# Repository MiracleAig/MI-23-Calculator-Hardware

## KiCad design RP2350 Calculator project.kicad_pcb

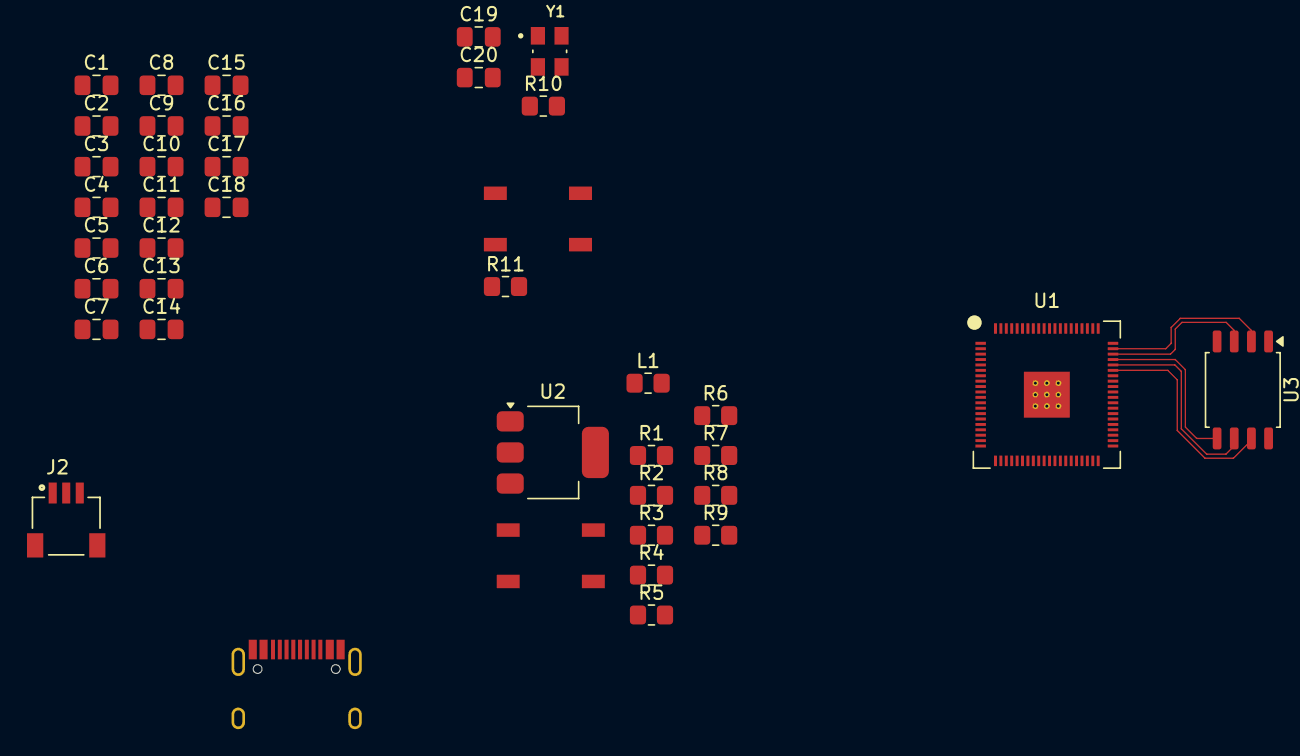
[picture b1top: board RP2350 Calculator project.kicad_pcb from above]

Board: 2 copper layers, 40 parts (0 on the bottom side), 28 nets.

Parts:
C1, C2, C3, C16: 4.7uF; C_0805_2012Metric_Pad1.18x1.45mm_HandSolder
C4, C5: 10u; C_0805_2012Metric_Pad1.18x1.45mm_HandSolder
C6, C7, C8, C9, C10, C11, C12, C13, C14, C15, C17, C18: 100n; C_0805_2012Metric_Pad1.18x1.45mm_HandSolder
C19, C20: 15pF; C_0805_2012Metric_Pad1.18x1.45mm_HandSolder
J1: USB_C_Receptacle_USB2.0_14P; USB_C_HRO_TYPE-C-31-M-12
J2: SM03B-SRSS-TB_LF__SN_; JST_SM03B-SRSS-TB_LF__SN_
L1: 3.3u; R_0805_2012Metric_Pad1.20x1.40mm_HandSolder
R1: 33; R_0805_2012Metric_Pad1.20x1.40mm_HandSolder
R2, R3: 5.1K; R_0805_2012Metric_Pad1.20x1.40mm_HandSolder
R4, R5: 27; R_0805_2012Metric_Pad1.20x1.40mm_HandSolder
R6, R7, R8: DNF; R_0805_2012Metric_Pad1.20x1.40mm_HandSolder
R9, R10, R11: 1K; R_0805_2012Metric_Pad1.20x1.40mm_HandSolder
SW1, SW2: SW_Push; Button_TL3342
U1: RP2350A-QFN60; RP2350B_QFN-80_EP_10.573x10.573_Pitch0.4mm
U2: NCP1117-3.3_SOT223; NCP1117_3V3
U3: W25Q128JVS
Y1: ABM8-272-T3; XTAL_ABM8-272-T3

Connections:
+1V1: C1.1, C15.1, C16.1, C17.1, L1.1, U1.6 (DVDD), U1.23 (DVDD), U1.39 (DVDD), U1.50 (VREG_FB)
+3V3: C2.1, C5.1, C6.1, C7.1, C8.1, C9.1, C10.1, C11.1, C12.1, C13.1, C14.1, C18.2, R1.1, R6.1, U1.1 (IOVDD), U1.11 (IOVDD), U1.20 (IOVDD), U1.30 (IOVDD), U1.38 (IOVDD), U1.44 (ADC_AVDD), U1.45 (IOVDD), U1.49 (VREG_VIN), U1.53 (USB_OTP_VDD), U1.54 (QSPI_IOVDD), U2.2 (VO), U3.8 (VCC)
D+: J1.A6 (D+), J1.B6 (D+), R4.1
D-: J1.A7 (D-), J1.B7 (D-), R5.2
GND: C1.2, C2.2, C3.2, C4.2, C5.2, C6.2, C7.2, C8.2, C9.2, C10.2, C11.2, C12.2, C13.2, C14.2, C15.2, C16.2, C17.2, C18.1, C19.1, C20.1, J1.A1 (GND), J1.A12 (GND), J1.B1 (GND), J1.B12 (GND), J1.S1 (SHIELD), J2.2, J2.S1 (SHIELD), J2.S2 (SHIELD), R2.2, R3.2, R11.1, SW1.1, U1.47 (VREG_PGND), U1.61 (GND), U2.1 (GND), U3.4 (GND), Y1.2 (GND), Y1.4 (GND)
GPIO0: R8.1, U1.2 (GPIO0)
unnamed: C20.2, R10.1, Y1.3
unnamed: J1.A5 (CC1), R2.1
unnamed: J1.B5 (CC2), R3.1
unnamed: R9.1, SW1.2
unnamed: R11.2, SW2.1
unnamed: R5.1, U1.51 (USB_DM)
unnamed: R4.2, U1.52 (USB_DP)
unnamed: C3.1, R1.2, U1.46 (VREG_AVDD)
unnamed: L1.2, U1.48 (VREG_LX)
unnamed: R6.2, R7.2, R8.2, U3.1 (~CS)
QSPI_SCLK: U1.56 (QSPI_SCLK), U3.6 (CLK)
QSPI_SD0: U1.57 (QSPI_SD0), U3.5 (DI/IO_{0})
QSPI_SD1: U1.59 (QSPI_SD1), U3.2 (DO/IO_{1})
QSPI_SD2: U1.58 (QSPI_SD2), U3.3 (~WP/IO_{2})
QSPI_SD3: U1.55 (QSPI_SD3), U3.7 (~HOLD/~RESET/IO_{3})
QSPI_SS: R7.1, R9.2, U1.60 (QSPI_SS)
RESET: SW2.2, U1.26 (RUN)
SWCLK: J2.1, U1.24 (SWCLK)
SWD: J2.3, U1.25 (SWDIO)
VBUS: C4.1, J1.A4 (VBUS), J1.A9 (VBUS), J1.B4 (VBUS), J1.B9 (VBUS), U2.3 (VI)
XIN: C19.2, U1.21 (XIN), Y1.1
XOUT: R10.2, U1.22 (XOUT)

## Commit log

2026-03-20 Initial commit - RP2350 calculator Project files
